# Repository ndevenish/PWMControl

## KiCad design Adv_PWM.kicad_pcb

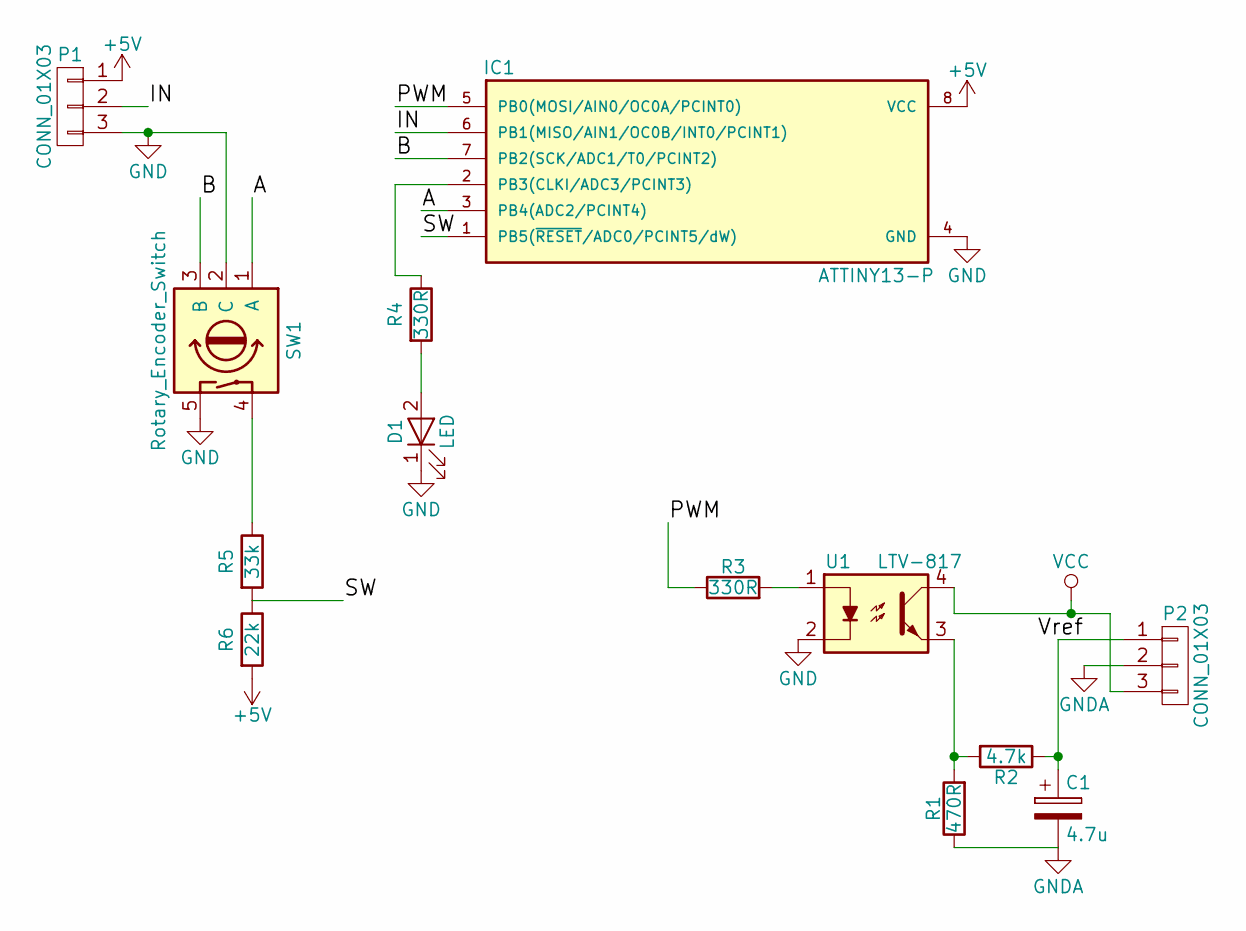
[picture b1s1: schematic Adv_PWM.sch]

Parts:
C1: 4.7u; CP_Radial_D5.0mm_P2.50mm
D1: LED; LED_D3.0mm
IC1: ATTINY13-P; DIP-8_W7.62mm
P1, P2: CONN_01X03; Pin_Header_Straight_1x03_Pitch2.54mm
R1: 470R; R_Axial_DIN0204_L3.6mm_D1.6mm_P5.08mm_Horizontal
R2: 4.7k; R_Axial_DIN0204_L3.6mm_D1.6mm_P5.08mm_Horizontal
R3: 330R; R_Axial_DIN0204_L3.6mm_D1.6mm_P5.08mm_Horizontal
R4: 330R; R_0805_HandSoldering
R5: 33k; R_Axial_DIN0204_L3.6mm_D1.6mm_P5.08mm_Horizontal
R6: 22k; R_Axial_DIN0204_L3.6mm_D1.6mm_P5.08mm_Horizontal
SW1: Rotary_Encoder_Switch; Rotary
U1: LTV-817; DIP-4_W7.62mm

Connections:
+5V: IC1.8 (VCC), P1.1, R6.2
/A: IC1.3 (PB4(ADC2/PCINT4)), SW1.1 (A)
/B: IC1.7 (PB2(SCK/ADC1/T0/PCINT2)), SW1.3 (B)
/IN: IC1.6 (PB1(MISO/AIN1/OC0B/INT0/PCINT1)), P1.2
/PWM: IC1.5 (PB0(MOSI/AIN0/OC0A/PCINT0)), R3.1
/SW: IC1.1 (PB5(~RESET~/ADC0/PCINT5/dW)), R5.2, R6.1
/Vref: C1.1, P2.1, R2.1
GND: D1.1 (K), IC1.4 (GND), P1.3, SW1.2 (C), SW1.5, U1.2
GNDA: C1.2, P2.2, R1.1
unnamed: D1.2 (A), R4.2
unnamed: IC1.2 (PB3(CLKI/ADC3/PCINT3)), R4.1
unnamed: R1.2, R2.2, U1.3
unnamed: R3.2, U1.1
unnamed: R5.1, SW1.4
VCC: P2.3, U1.4

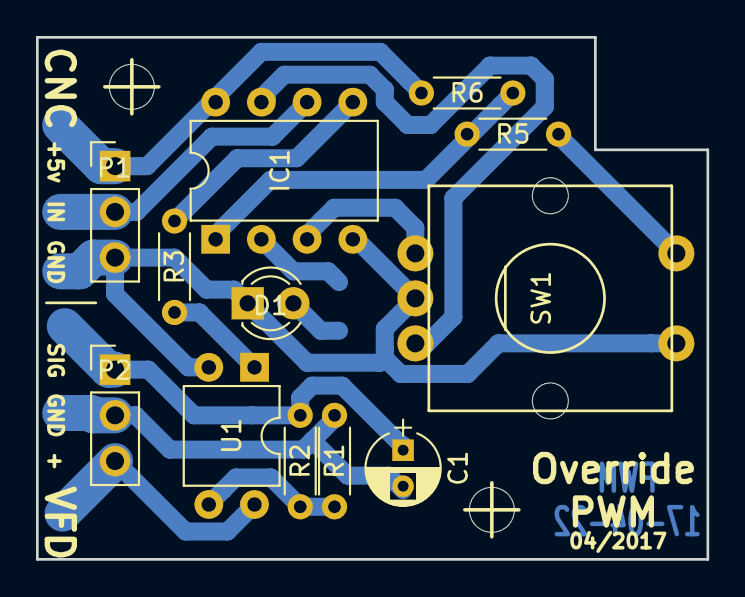
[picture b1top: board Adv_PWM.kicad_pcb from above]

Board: 2 copper layers, 37.2 x 29.0 mm, 13 parts (1 on the bottom side), 15 nets.

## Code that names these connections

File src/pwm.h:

/*
 * pwm.h
 *
 * Created: 24/04/2017 15:27:54
 *  Author: misno
 */ 

#include <stdint.h>

#ifndef PWM_H_
#define PWM_H_

// Pin assignments
#define PIN_PWM_OUT PB0
#define PIN_PWM_IN  PB1
#define PIN_ROT_B   PB2
#define PIN_LED     PB3
#define PIN_ROT_A   PB4

#define PIN_ROT_SW  PB5
#define ADC_SW      ADC0


uint32_t read_cycle_ASM();


// Define this to use interrupt and timer-based PWM measurement
//#define PWM_INTERRUPT






#endif /* PWM_H_ */

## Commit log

2017-04-16 Original cut
2017-04-16 INT0 changes
2017-04-16 Start writing firmware
2017-04-22 Compactify a little more
    This includes adding a single surface mount resistor!
2017-04-22 More steps to firmware infrastructure
2017-04-22 Add the millproject file for PCB2GCode
2017-04-22 Switch the PWM output to a clock pin
2017-04-22 Use Voltage Divider on reset pin
    this means that we no longer need the reset fuse to be set, allowing
    reprogramming when testing. This required the swapping of pins and a
    slightly more complicated board.
2017-04-22 Start setting up pins and layout out code
2017-04-23 Add an atmel studio solution
2017-04-24 Change the capacitor footprint to be smaller
2017-04-24 Rename silkscreen label
2017-04-24 First draft of pwm reading with stimfile
2017-04-24 Write the pulse-read code in assembly for timing
    Both high and low-reading loops need to be exactly the same length in
    clock ticks
2017-04-24 Use 13 cycles/loop instead
2017-04-24 Tidy assembly and abstract loop size
2017-04-24 Be clearer about IO access
2017-04-24 Change duty cycle calculations and test
2017-04-24 Correct faulty inverting logic in assembly
2017-04-24 Fix for 100% duty cycle overflow
2017-04-24 Fix the asm source file for the inverting logic
2017-04-24 Fix PWM duty cycle calculation
2017-04-24 More assembly descriptions
2017-04-24 Scale back the timer when speeding up the CPU
    That way, the PWM output will stay stable and at the same frequency
    (4.7KHz at the moment)
2017-04-24 Simulator stimfile for stability and range of pulses
2017-04-25 Start writing an alternative, interrupt-based PWM reader
    This is controlled by a preprocessor flag in the header
2017-04-25 Ignore pdf files in gerber folder
2017-04-25 Ignore hidden visual studio folder
